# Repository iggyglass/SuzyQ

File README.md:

# Suzy Q
A simple implementation of a Chromebook self case closed debugger, allowing the Chromebook USB-CDC debug console to be accessed from the Chromebook itself. Note that this only works on Chromebooks and not Android devices, as Android devices in debug mode can act as USB devices and not hosts (which is how ADB works).

## Manufacturing Notes
Due to the edge-mount USB-C plug used, make sure to have the PCBs fabricated with a $0.8\textrm{ }\mathrm{mm}$ thickness.

## BOM
| Item                                     | Qty |
|------------------------------------------|-----|
| Molex 105444                             | 1   |
| $5.1\textrm{ }\mathrm{k\Omega}$ Resistor | 2   |

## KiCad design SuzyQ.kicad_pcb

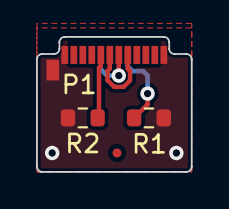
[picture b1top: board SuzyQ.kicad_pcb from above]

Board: 2 copper layers, 8.6 x 7.5 mm, 3 parts (0 on the bottom side), 5 nets.

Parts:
P1: USB_C_Plug; USB_C_Plug_Molex_105444
R1, R2: 5.1k; R_0603_1608Metric

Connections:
/D+: P1.A6 (D+), P1.A8 (SBU1)
/D-: P1.A7 (D-), P1.B8 (SBU2)
GND: P1.A1 (GND), P1.A12 (GND), P1.B1 (GND), P1.B12 (GND), P1.S1 (SHIELD), R1.2, R2.2
unnamed: P1.A5 (CC), R2.1
unnamed: P1.B5 (VCONN), R1.1

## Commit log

2024-08-03 Radius'd PCB corners, added fiducial
